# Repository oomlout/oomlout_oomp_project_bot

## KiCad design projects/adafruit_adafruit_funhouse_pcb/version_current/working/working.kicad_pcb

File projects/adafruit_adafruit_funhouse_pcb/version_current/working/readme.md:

# Adafruit-FunHouse-PCB by adafruit  
This is a harvested standardized copy of a project from github.  
The original project can be found at:  
https://github.com/adafruit/Adafruit-FunHouse-PCB  
Please consult that link for additional, details, files, and license information.  
Note: It was auto harvested and if the original repo had more than one board file or anything out of the ordinary the files here are likely not representative.

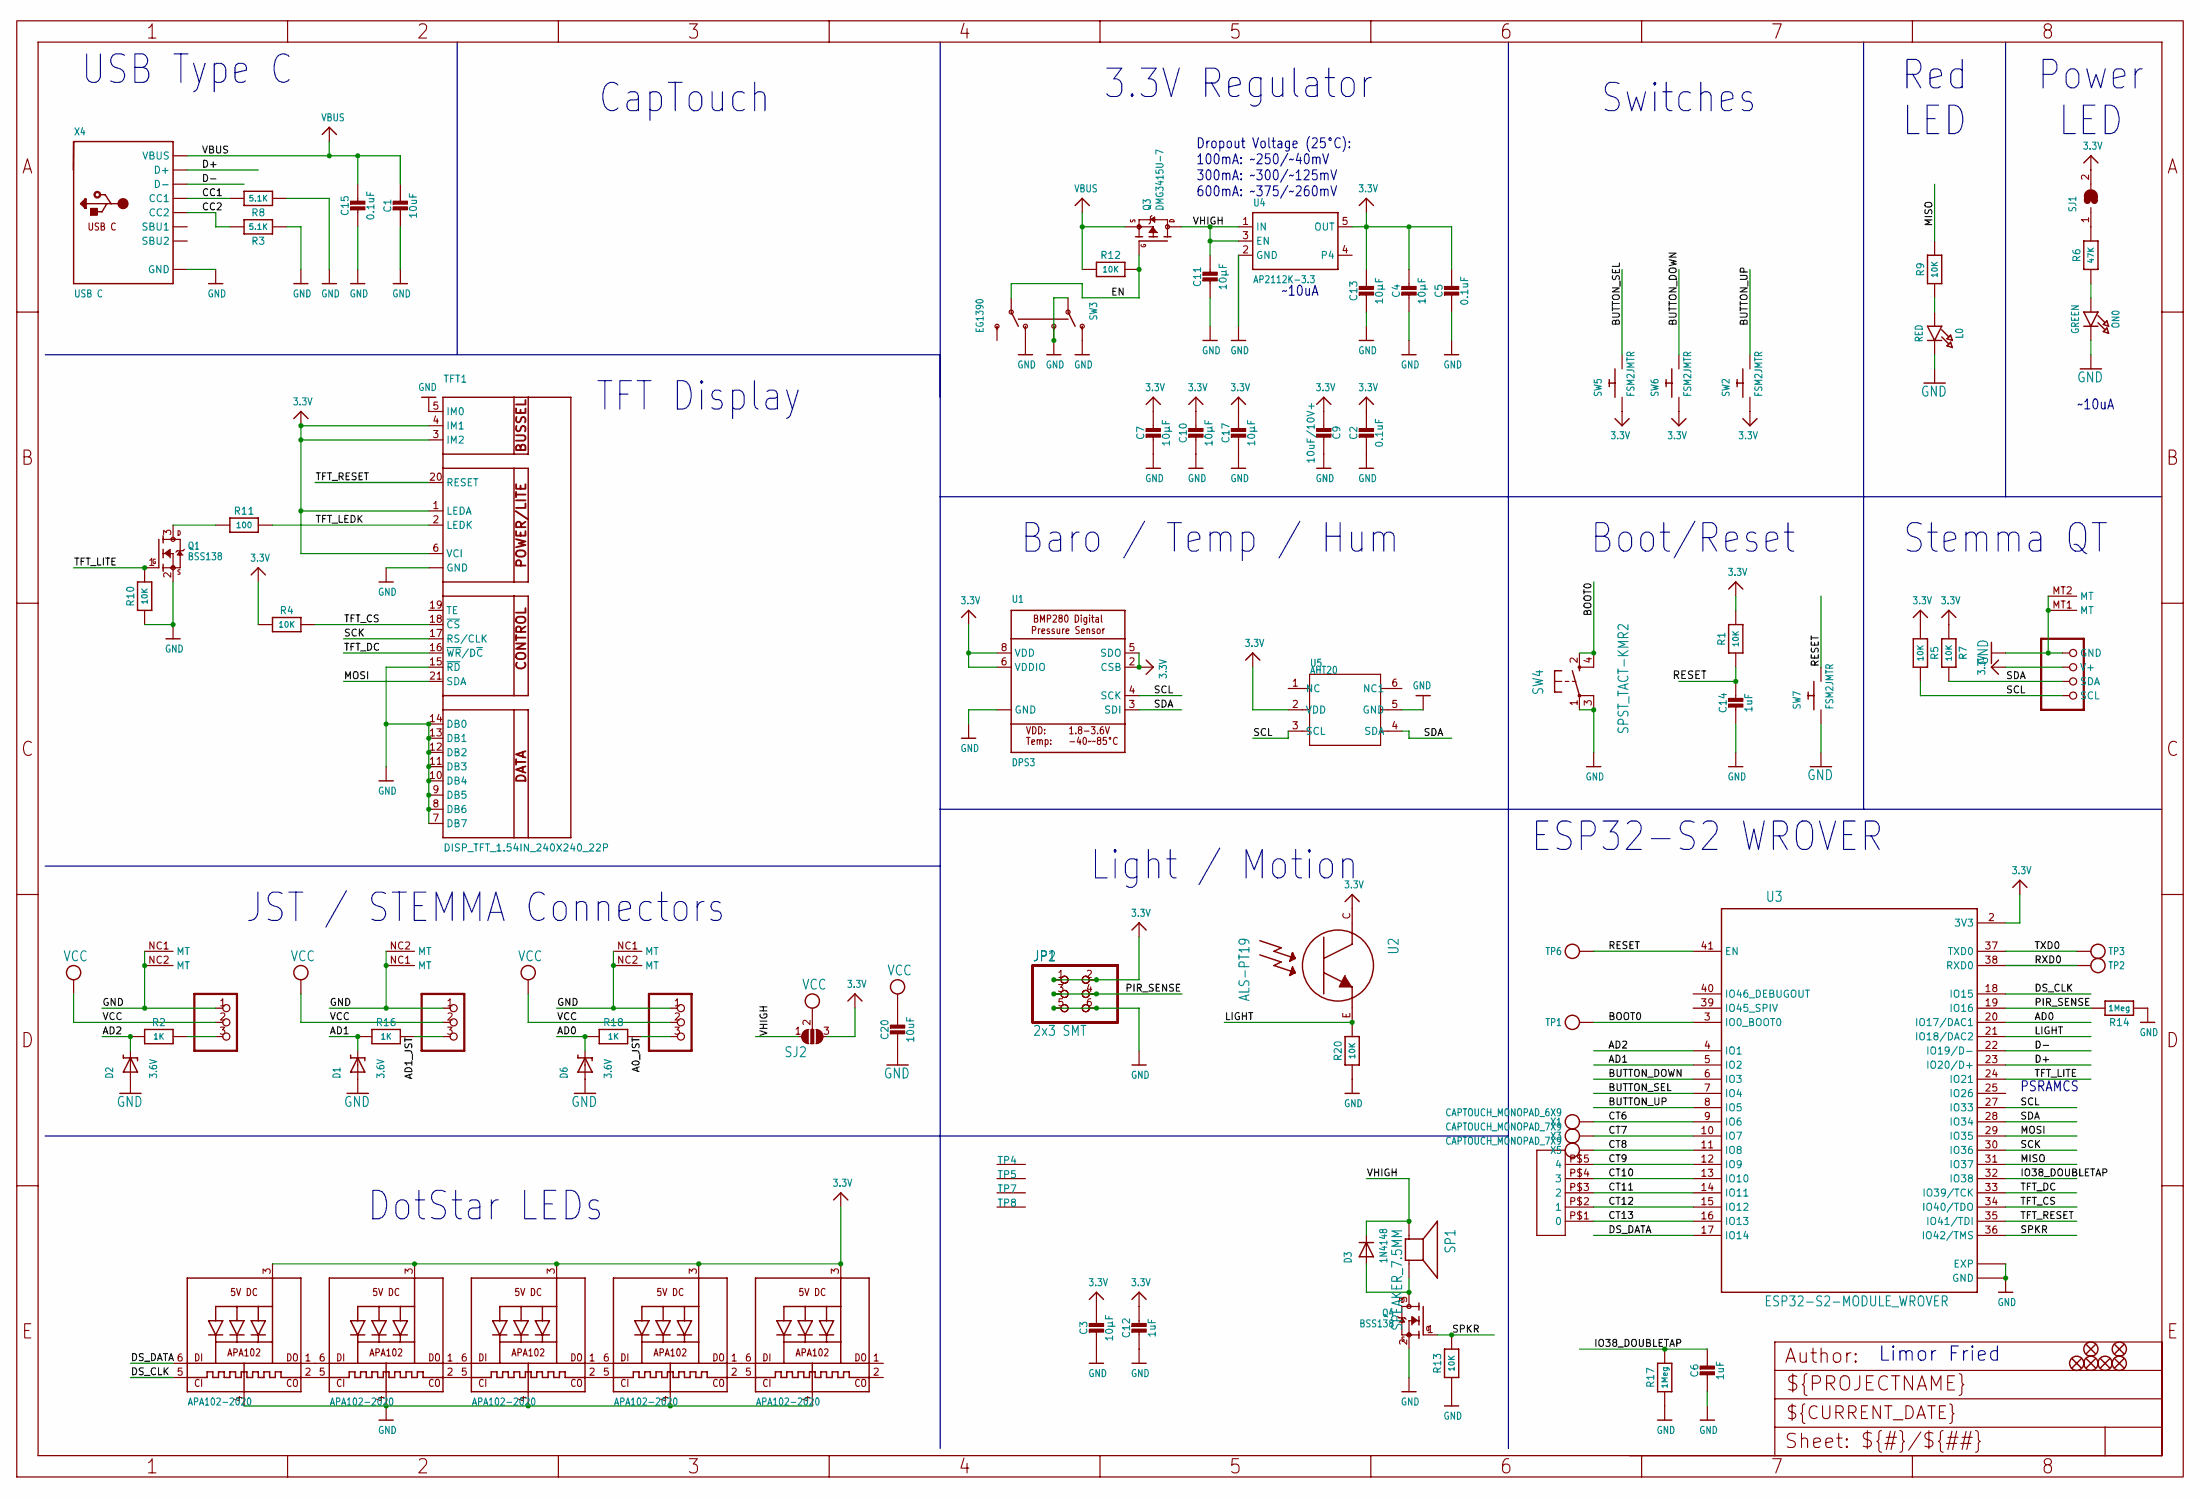
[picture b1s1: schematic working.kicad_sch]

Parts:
C1, C20: 10uF; 0805-NO
C2, C5, C15: 0.1uF; 0603-NO
C3, C4, C7, C10, C11, C13, C17: 10µF; 0805-NO
C6, C12, C14: 1uF; 0603-NO
C9: 10uF/10V+; 0805_10MGAP
CONN1: STEMMA_I2C_QT; JST_SH4
D1, D2, D6: 3.6V; SOD-323
D3: 1N4148; SOD-323F
DS0, DS1, DS2, DS3, DS4: APA102-2020; APA102_2020
FID1, FID2, FID3, FID4, FID5, FID6: FIDUCIAL_1MM
JP1: 2x3 SMT; 2X03_SMT_4UCON_14113
JP2: HEADER-2X3_SMTTHM; 2X03_SMTTHM
L0: RED; CHIPLED_0603_NOOUTLINE
ON0: GREEN; CHIPLED_0603_NOOUTLINE
Q1: BSS138; SOT23-WIDE
Q3: DMG3415U-7; SOT23-R
Q4: BSS138; SOT23-R
R1, R4, R5, R7, R9, R10, R12, R13, R20: 10K; 0603-NO
R2, R16, R18: 1K; 0603-NO
R3, R8: 5.1K; 0603-NO
R6: 47K; 0603-NO
R11: 100; 0603-NO
R14, R17: 1Meg; 0603-NO
SENSE0, SENSE1, SENSE3: JST PH 3; JSTPH3
SJ1: SOLDERJUMPERCLOSED; SOLDERJUMPER_CLOSEDWIRE
SJ2: SOLDERJUMPER_2WAY; SOLDERJUMPER_2WAY_OPEN_NOPASTE
SP1: SPEAKER_7.5MM; BUZZER_SMT_7.5MM
SW2, SW5, SW6, SW7: FSM2JMTR; TACTILE_3X6MM
SW3: EG1390
SW4: SPST_TACT-KMR2; KMR2
TFT1: DISP_TFT_1.54IN_240X240_22P; TFT_1.54IN_240X240_22PIN
TP1, TP2, TP3, TP6: TESTPOINTROUND1.5MMNO; TESTPOINT_ROUND_1.5MM_NO
TP4, TP5, TP7, TP8: SEWTAP_SMTNUTM3; SMT_NUT_3MM
U1: DPS3; BMX280_COMBO
U2: ALS-PT19; ALS-PT19-315C
U3: ESP32-S2-MODULE_WROVER; MODULE_ESP32-S2-WROVER
U4: AP2112K-3.3; SOT23-5
U5: AHT20; SNR6-1.0-3X3X1MM
X1: CAPTOUCH_MONOPAD_6X9; CAPTOUCH_6X9MM
X3, X5: CAPTOUCH_MONOPAD_7X9; CAPTOUCH_7X9MM
X4: USB C; USB_C_CUSB31-CFM2AX-01-X
X6: CAPTOUCH_5SLIDER_10MM; CAPTOUCH_5SLIDER

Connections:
3.3V: C2.1, C3.1, C4.1, C5.1, C7.1, C9.2, C10.1, C12.1, C13.1, C17.1, CONN1.2 (V+), DS0.3 (VDD), DS1.3 (VDD), DS2.3 (VDD), DS3.3 (VDD), DS4.3 (VDD), JP1.1, JP1.2, JP2.1, JP2.2, JP2.T1 (1), JP2.T2 (2), R1.2, R4.1, R5.1, R7.1, SJ1.2, SJ2.3, SW2.P$1, SW5.P$1, SW6.P$1, TFT1.1 (LEDA), TFT1.3 (IM2), TFT1.4 (IM1), TFT1.6 (VCI), U1.2 (CSB), U1.5 (SDO), U1.6 (VDDIO), U1.8 (VDD), U2.C, U3.2 (3V3), U4.5 (OUT), U5.2 (VDD)
A0_JST: R18.1, SENSE1.3
A2_JST2: R2.1, SENSE3.3
AD0: D6.C, R18.2, U3.20 (IO17/DAC1)
AD1: D1.C, R16.2, U3.5 (IO2)
AD1_JST: R16.1, SENSE0.3
AD2: D2.C, R2.2, U3.4 (IO1)
BOOT0: SW4.2 (S), SW4.4 (S1), TP1.P$1, U3.3 (IO0_BOOT0)
BUTTON_DOWN: SW6.P$2, U3.6 (IO3)
BUTTON_SEL: SW5.P$2, U3.7 (IO4)
BUTTON_UP: SW2.P$2, U3.8 (IO5)
CC1: R8.2, X4.A5 (CC1)
CC2: R3.2, X4.B5 (CC2)
CT6: U3.9 (IO6), X1.P$1
CT7: U3.10 (IO7), X3.P$1
CT8: U3.11 (IO8), X5.P$1
CT9: U3.12 (IO9), X6.P$5 (4)
CT10: U3.13 (IO10), X6.P$4 (3)
CT11: U3.14 (IO11), X6.P$3 (2)
CT12: U3.15 (IO12), X6.P$2 (1)
CT13: U3.16 (IO13), X6.P$1 (0)
D+: U3.23 (IO20/D+), X4.A6 (D+), X4.B6 (D+)
D-: U3.22 (IO19/D-), X4.A7 (D-), X4.B7 (D-)
DS_CLK: DS0.5 (CKI), U3.18 (IO15)
DS_DATA: DS0.6 (DI), U3.17 (IO14)
EN: Q3.1 (G), R12.2, SW3.P2
GND: C1.2, C2.2, C3.2, C4.2, C5.2, C6.2, C7.2, C9.1, C10.2, C11.2, C12.2, C13.2, C14.2, C15.2, C17.2, C20.2, CONN1.1 (GND), CONN1.MT1 (MT), CONN1.MT2 (MT), D1.A, D2.A, D6.A, DS0.4 (GND), DS1.4 (GND), DS2.4 (GND), DS3.4 (GND), DS4.4 (GND), JP1.5, JP1.6, JP2.5, JP2.6, JP2.T5 (5), JP2.T6 (6), L0.C, ON0.C, Q1.2 (S), Q4.2 (S), R3.1, R8.1, R10.1, R13.1, R14.1, R17.1, R20.1, SENSE0.1, SENSE0.NC1 (MT), SENSE0.NC2 (MT), SENSE1.1, SENSE1.NC1 (MT), SENSE1.NC2 (MT), SENSE3.1, SENSE3.NC1 (MT), SENSE3.NC2 (MT), SW3.O1, SW3.O2, SW3.P1, SW3.S1, SW4.1, SW4.3 (P1), SW7.P$1, TFT1.5 (IM0), TFT1.7 (DB7), TFT1.8 (DB6), TFT1.9 (DB5), TFT1.10 (DB4), TFT1.11 (DB3), TFT1.12 (DB2), TFT1.13 (DB1), TFT1.14 (DB0), TFT1.15 (~RD), TFT1.22 (GND), TFT1.SUPPORT1 (GND), TFT1.SUPPORT2 (GND), U1.1 (GND), U1.7 (GND), U3.1 (GND), U3.26 (GND), U3.42 (GND), U3.43_1 (EXP), U3.43_2 (EXP), U3.43_3 (EXP), U3.43_4 (EXP), U3.43_5 (EXP), U3.43_6 (EXP), U3.43_7 (EXP), U3.43_8 (EXP), U3.43_9 (EXP), U3.43_10 (EXP), U3.43_11 (EXP), U3.43_12 (EXP), U3.43_13 (EXP), U3.43_14 (EXP), U3.43_15 (EXP), U3.43_16 (EXP), U3.43_17 (EXP), U3.43_18 (EXP), U3.43_19 (EXP), U3.43_20 (EXP), U3.43_21 (EXP), U4.2 (GND), U5.5 (GND), X4.A1B12 (GND), X4.B1A12 (GND)
IO38_DOUBLETAP: C6.1, R17.2, U3.32 (IO38)
LIGHT: R20.2, U2.E, U3.21 (IO18/DAC2)
MISO: R9.2, U3.31 (IO37)
MOSI: TFT1.21 (SDA), U3.29 (IO35)
unnamed: L0.A, R9.1
unnamed: R6.2, SJ1.1
unnamed: ON0.A, R6.1
unnamed: D3.A, Q4.3 (D), SP1.-
unnamed: DS0.1 (DO), DS1.6 (DI)
unnamed: DS0.2 (CKO), DS1.5 (CKI)
unnamed: DS1.1 (DO), DS2.6 (DI)
unnamed: DS1.2 (CKO), DS2.5 (CKI)
unnamed: DS2.1 (DO), DS3.6 (DI)
unnamed: DS2.2 (CKO), DS3.5 (CKI)
unnamed: DS3.1 (DO), DS4.6 (DI)
unnamed: DS3.2 (CKO), DS4.5 (CKI)
unnamed: Q1.3 (D), R11.1
PIR_SENSE: JP1.3, JP1.4, JP2.3, JP2.4, JP2.T3 (3), JP2.T4 (4), R14.2, U3.19 (IO16)
RESET: C14.1, R1.1, SW7.P$2, TP6.P$1, U3.41 (EN)
RXD0: TP2.P$1, U3.38 (RXD0)
SCK: TFT1.17 (RS/CLK), U3.30 (IO36)
SCL: CONN1.4 (SCL), R5.2, U1.4 (SCK), U3.27 (IO33), U5.3 (SCL)
SDA: CONN1.3 (SDA), R7.2, U1.3 (SDI), U3.28 (IO34), U5.4 (SDA)
SPKR: Q4.1 (G), R13.2, U3.36 (IO42/TMS)
TFT_CS: R4.2, TFT1.18 (~CS), U3.34 (IO40/TDO)
TFT_DC: TFT1.16 (~WR/D~C), U3.33 (IO39/TCK)
TFT_LEDK: R11.2, TFT1.2 (LEDK)
TFT_LITE: Q1.1 (G), R10.2, U3.24 (IO21)
TFT_RESET: TFT1.20 (RESET), U3.35 (IO41/TDI)
TXD0: TP3.P$1, U3.37 (TXD0)
VBUS: C1.1, C15.1, Q3.2 (S), R12.1, X4.A4B9 (VBUS), X4.B4A9 (VBUS)
VCC: C20.1, SENSE0.2, SENSE1.2, SENSE3.2, SJ2.2
VHIGH: C11.1, D3.C, Q3.3 (D), SJ2.1, SP1.+, U4.1 (IN), U4.3 (EN)

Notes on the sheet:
Baro / Temp / Hum
~10uA
JST / STEMMA Connectors
CapTouch
ESP32-S2 WROVER
Red LED
3.3V Regulator
Dropout Voltage (25°C): 100mA: ~250/~40mV 300mA: ~300/~125mV 600mA: ~375/~260mV
Stemma QT
PSRAMCS
Limor Fried
Boot/Reset
Switches
DotStar LEDs
USB Type C
TFT Display
Power LED
Light / Motion

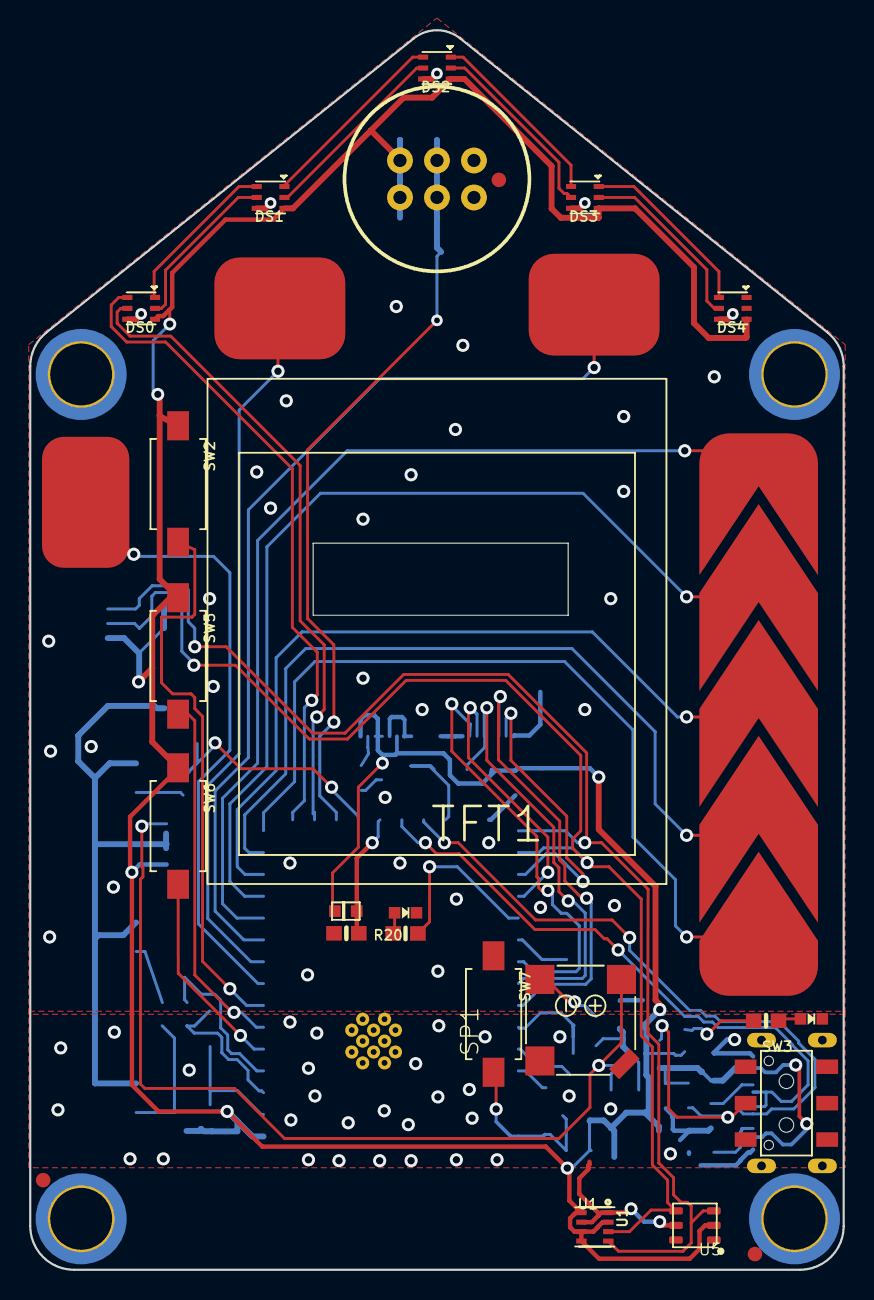
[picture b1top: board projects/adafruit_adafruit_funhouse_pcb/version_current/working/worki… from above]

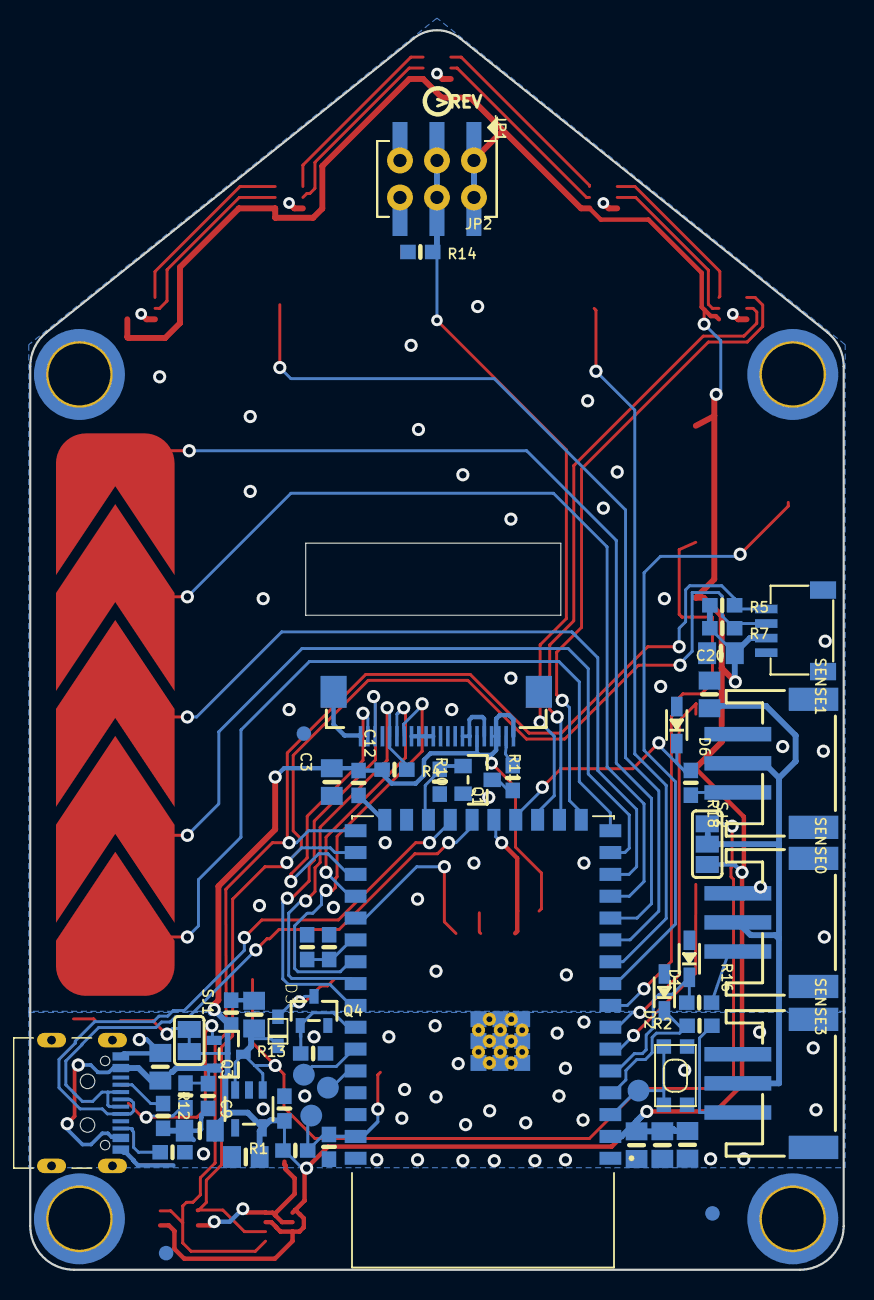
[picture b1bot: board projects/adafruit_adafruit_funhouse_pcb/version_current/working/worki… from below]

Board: 2 copper layers, 55.9 x 85.1 mm, 91 parts (63 on the bottom side), 60 nets.

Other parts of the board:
U$41: PCBFEAT-REV-040
U$45: FUNHOUSE_FRONT
U$69: FUNHOUSE_BACK

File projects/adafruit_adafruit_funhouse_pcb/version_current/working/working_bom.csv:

Row,Description,Part,References,Value,Footprint,Quantity Per PCB,Status,Datasheet
1,,CAP_CERAMIC0603_NO,C2 C5 C15,0.1uF,0603-NO,3, ,
2,,CAP_CERAMIC0603_NO,C6 C12 C14,1uF,0603-NO,3, ,
3,,CAP_CERAMIC0805-NOOUTLINE,C1 C3 C4 C7 C10 C11 C13 C17 C20,10uF,0805-NO,9, ,
4,,CAP_CERAMIC0805_10MGAP,C9,10uF/10V+,0805_10MGAP,1, ,
5,,STEMMA_I2C_QT,CONN1,STEMMA_I2C_QT,JST_SH4,1, ,
6,,DIODESOD-323F,D3,1N4148,SOD-323F,1, ,
7,,DIODE-ZENERSOD323,D1 D2 D6,3.6V,SOD-323,3, ,
8,,APA1022020,DS0 DS1 DS2 DS3 DS4,APA102-2020,APA102_2020,5, ,
9,,HEADER-2X314113,JP1,2x3 SMT,2X03_SMT_4UCON_14113,1, ,
10,,HEADER-2X3_SMTTHM,JP2,HEADER-2X3_SMTTHM,2X03_SMTTHM,1, ,
11,,LED0603_NOOUTLINE,L0,RED,CHIPLED_0603_NOOUTLINE,1, ,
12,,LED0603_NOOUTLINE,ON0,GREEN,CHIPLED_0603_NOOUTLINE,1, ,
13,,MOSFET-NWIDE,Q1,BSS138,SOT23-WIDE,1, ,
14,,MOSFET-NREFLOW,Q4,BSS138,SOT23-R,1, ,
15,,MOSFET-P,Q3,DMG3415U-7,SOT23-R,1, ,
16,,RESISTOR_0603_NOOUT,R11,100,0603-NO,1, ,
17,,RESISTOR_0603_NOOUT,R2 R16 R18,1K,0603-NO,3, ,
18,,RESISTOR_0603_NOOUT,R3 R8,5.1K,0603-NO,2, ,
19,,RESISTOR_0603_NOOUT,R1 R4 R5 R7 R9 R10 R12 R13 R20,10K,0603-NO,9, ,
20,,RESISTOR_0603_NOOUT,R6,47K,0603-NO,1, ,
21,,RESISTOR_0603_NOOUT,R14 R17,1Meg,0603-NO,2, ,
22,,CON_JST_PH_3PIN,SENSE0 SENSE1 SENSE3,JST PH 3,JSTPH3,3, ,
23,,SPEAKER_7.5MM,SP1,SPEAKER_7.5MM,BUZZER_SMT_7.5MM,1, ,
24,,SWITCH_DPDTEG1390,SW3,EG1390,EG1390,1, ,
25,,adafruit_electromech_SWITCH_PUSHBUTTON_3.5X6MM,SW2 SW5 SW6,FSM2JMTR,TACTILE_3X6MM,3, ,
26,,SWITCH_PUSHBUTTON_3.5X6MM,SW7,FSM2JMTR,TACTILE_3X6MM,1, ,
27,,SPST_TACT-KMR2,SW4,SPST_TACT-KMR2,KMR2,1, ,
28,,DISP_TFT_1.54IN_240X240_22P,TFT1,DISP_TFT_1.54IN_240X240_22P,TFT_1.54IN_240X240_22PIN,1, ,
29,,SENSOR-AHT20,U5,AHT20,SNR6-1.0-3X3X1MM,1, ,
30,,PHOTOTRANSISTOR_PT19-315C,U2,ALS-PT19,ALS-PT19-315C,1, ,
31,,VREG_SOT23-5,U4,AP2112K-3.3,SOT23-5,1, ,
32,,BMP280_COMBO,U1,DPS3,BMX280_COMBO,1, ,
33,,ESP32-S2-MODULE_WROVER,U3,ESP32-S2-MODULE_WROVER,MODULE_ESP32-S2-WROVER,1, ,
34,,CAPTOUCH_5SLIDER_10MM,X6,CAPTOUCH_5SLIDER_10MM,CAPTOUCH_5SLIDER,1, ,
35,,CAPTOUCH_MONOPAD_6X9,X1,CAPTOUCH_MONOPAD_6X9,CAPTOUCH_6X9MM,1, ,
36,,CAPTOUCH_MONOPAD_7X9,X3 X5,CAPTOUCH_MONOPAD_7X9,CAPTOUCH_7X9MM,2, ,
37,,USB_C,X4,USB C,USB_C_CUSB31-CFM2AX-01-X,1, ,





Project info:
Schematic:,working
Variant:,default
Revision:,
Date:,2023-08-06_12-55-57
KiCad Version:,7.0.6-7.0.6~ubuntu22.04.1
Statistics:
Component Groups:,37
Component Count:,72 (0 SMD/ 0 THT)
Fitted Components:,72 (0 SMD/ 0 THT)
Number of PCBs:,1
Total Components:,72

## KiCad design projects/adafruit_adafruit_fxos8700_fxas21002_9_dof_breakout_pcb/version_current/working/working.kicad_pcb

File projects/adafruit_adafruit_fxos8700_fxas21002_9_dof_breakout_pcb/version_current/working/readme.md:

# Adafruit-FXOS8700-FXAS21002-9-DoF-Breakout-PCB by adafruit  
This is a harvested standardized copy of a project from github.  
The original project can be found at:  
https://github.com/adafruit/Adafruit-FXOS8700-FXAS21002-9-DoF-Breakout-PCB  
Please consult that link for additional, details, files, and license information.  
Note: It was auto harvested and if the original repo had more than one board file or anything out of the ordinary the files here are likely not representative.

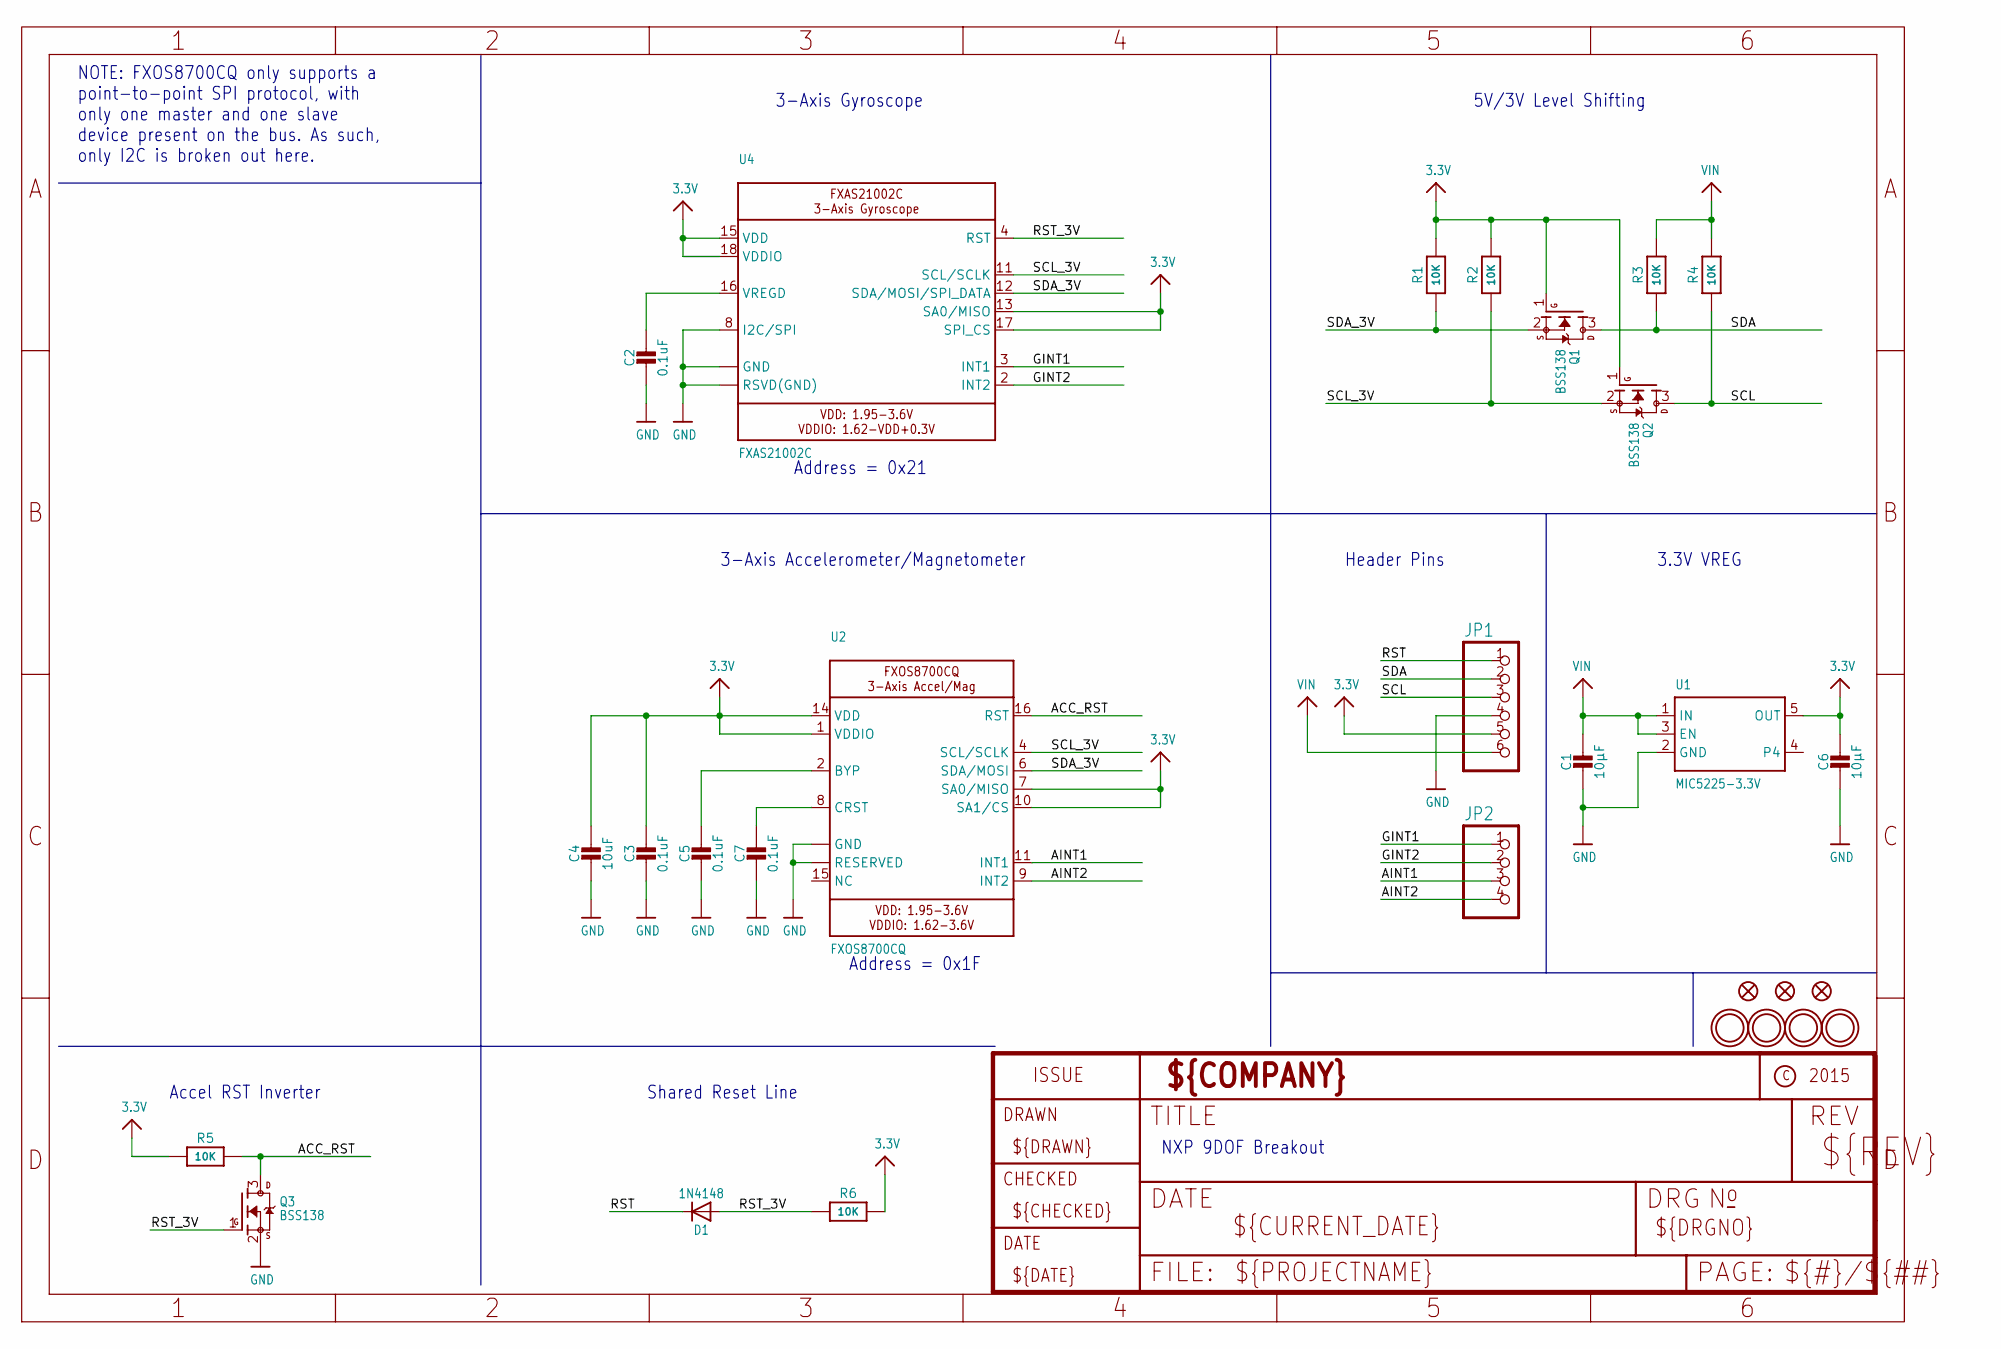
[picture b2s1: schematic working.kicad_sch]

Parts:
C1, C6: 10µF; 0805-NO
C2, C3, C5, C7: 0.1uF; 0805-NO
C4: 10uF; 0805-NO
D1: 1N4148; SOD-323
FID1, FID2, FID3: FIDUCIAL_1MM
JP1: HEADER-1X670MIL; 1X06_ROUND_70
JP2: HEADER-1X4ROUND; 1X04_ROUND
Q1, Q2, Q3: BSS138; SOT23-WIDE
R1, R2, R3, R4, R5, R6: 10K; 0805-NO
U1: MIC5225-3.3V; SOT23-5
U2: FXOS8700CQ; QFN16_3MM_FREESCALE_5X3
U4: FXAS21002C; QFN24_4MM_FREESCALE_7X5
U$1, U$2, U$3, U$4: MOUNTINGHOLE2.5; MOUNTINGHOLE_2.5_PLATED

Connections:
3.3V: C3.1, C4.1, C6.1, JP1.5, Q1.1 (G), Q2.1 (G), R1.2, R2.2, R5.1, R6.2, U1.5 (OUT), U2.1 (VDDIO), U2.7 (SA0/MISO), U2.10 (SA1/CS), U2.14 (VDD), U4.13 (SA0/MISO), U4.15 (VDD), U4.17 (SPI_CS), U4.18 (VDDIO)
ACC_RST: Q3.3 (D), R5.2, U2.16 (RST)
AINT1: JP2.3, U2.11 (INT1)
AINT2: JP2.4, U2.9 (INT2)
GINT1: JP2.1, U4.3 (INT1)
GINT2: JP2.2, U4.2 (INT2)
GND: C1.2, C2.2, C3.2, C4.2, C5.2, C6.2, C7.2, JP1.4, Q3.2 (S), U1.2 (GND), U2.3 (RESERVED), U2.5 (GND), U2.12 (GND), U2.13 (RESERVED), U4.1 (GND), U4.5 (GND), U4.6 (RSVD(GND)), U4.7 (RSVD(GND)), U4.8 (I2C/SPI), U4.9 (RSVD(GND)), U4.10 (RSVD(GND)), U4.14 (GND), U4.19 (GND), U4.20 (RSVD(GND)), U4.21 (RSVD(GND)), U4.22 (RSVD(GND)), U4.23 (RSVD(GND)), U4.24 (RSVD(GND))
unnamed: C2.1, U4.16 (VREGD)
unnamed: C5.1, U2.2 (BYP)
unnamed: C7.1, U2.8 (CRST)
RST: D1.C, JP1.1
RST_3V: D1.A, Q3.1 (G), R6.1, U4.4 (RST)
SCL: JP1.3, Q2.3 (D), R4.1
SCL_3V: Q2.2 (S), R2.1, U2.4 (SCL/SCLK), U4.11 (SCL/SCLK)
SDA: JP1.2, Q1.3 (D), R3.1
SDA_3V: Q1.2 (S), R1.1, U2.6 (SDA/MOSI), U4.12 (SDA/MOSI/SPI_DATA)
VIN: C1.1, JP1.6, R3.2, R4.2, U1.1 (IN), U1.3 (EN)

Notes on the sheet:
Address = 0x21
Address = 0x1F
3-Axis Accelerometer/Magnetometer
5V/3V Level Shifting
3-Axis Gyroscope
Shared Reset Line
3.3V VREG
NXP 9DOF Breakout
Accel RST Inverter
NOTE: FXOS8700CQ only supports a point-to-point SPI protocol, with only one master and one slave device present on the bus. As such, only I2C is broken out here.
Header Pins

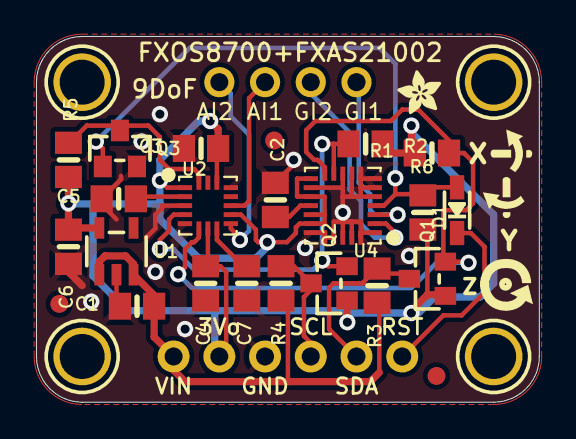
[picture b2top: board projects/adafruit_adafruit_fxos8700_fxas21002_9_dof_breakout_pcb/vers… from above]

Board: 2 copper layers, 27.9 x 20.3 mm, 34 parts (1 on the bottom side), 17 nets.

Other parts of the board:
U$26: ADAFRUIT_2.5MM
U$27: SYMBOL_GYRO_CCLOCKWISE
U$28: SYMBOL_GYRO_CLOCKWISE
U$31: SYMBOL_GYRO_Z
U$32: PCBFEAT-REV-040

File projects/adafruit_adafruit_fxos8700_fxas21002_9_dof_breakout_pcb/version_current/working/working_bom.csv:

Row,Description,Part,References,Value,Footprint,Quantity Per PCB,Status,Datasheet
1,,CAP_CERAMIC0805-NOOUTLINE,C2 C3 C5 C7,0.1uF,0805-NO,4, ,
2,,CAP_CERAMIC0805-NOOUTLINE,C1 C4 C6,10µF,0805-NO,3, ,
3,,DIODESOD-323,D1,1N4148,SOD-323,1, ,
4,,HEADER-1X4ROUND,JP2,HEADER-1X4ROUND,1X04_ROUND,1, ,
5,,HEADER-1X670MIL,JP1,HEADER-1X670MIL,1X06_ROUND_70,1, ,
6,,MOSFET-NWIDE,Q1 Q2 Q3,BSS138,SOT23-WIDE,3, ,
7,,RESISTOR0805_NOOUTLINE,R1 R2 R3 R4 R5 R6,10K,0805-NO,6, ,
8,,GYRO_FXAS21002C,U4,FXAS21002C,QFN24_4MM_FREESCALE_7X5,1, ,
9,,ACCEL_MAG_FXOS8700CQ,U2,FXOS8700CQ,QFN16_3MM_FREESCALE_5X3,1, ,
10,,VREG_SOT23-5,U1,MIC5225-3.3V,SOT23-5,1, ,





Project info:
Schematic:,working
Variant:,default
Revision:,
Date:,2023-08-03_17-21-22
KiCad Version:,7.0.6-7.0.6~ubuntu22.04.1
Statistics:
Component Groups:,10
Component Count:,22 (0 SMD/ 0 THT)
Fitted Components:,22 (0 SMD/ 0 THT)
Number of PCBs:,1
Total Components:,22

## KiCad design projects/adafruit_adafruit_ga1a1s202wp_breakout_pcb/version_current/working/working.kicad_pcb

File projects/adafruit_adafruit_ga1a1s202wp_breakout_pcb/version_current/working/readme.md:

# Adafruit-GA1A1S202WP-Breakout-PCB by adafruit  
This is a harvested standardized copy of a project from github.  
The original project can be found at:  
https://github.com/adafruit/Adafruit-GA1A1S202WP-Breakout-PCB  
Please consult that link for additional, details, files, and license information.  
Note: It was auto harvested and if the original repo had more than one board file or anything out of the ordinary the files here are likely not representative.

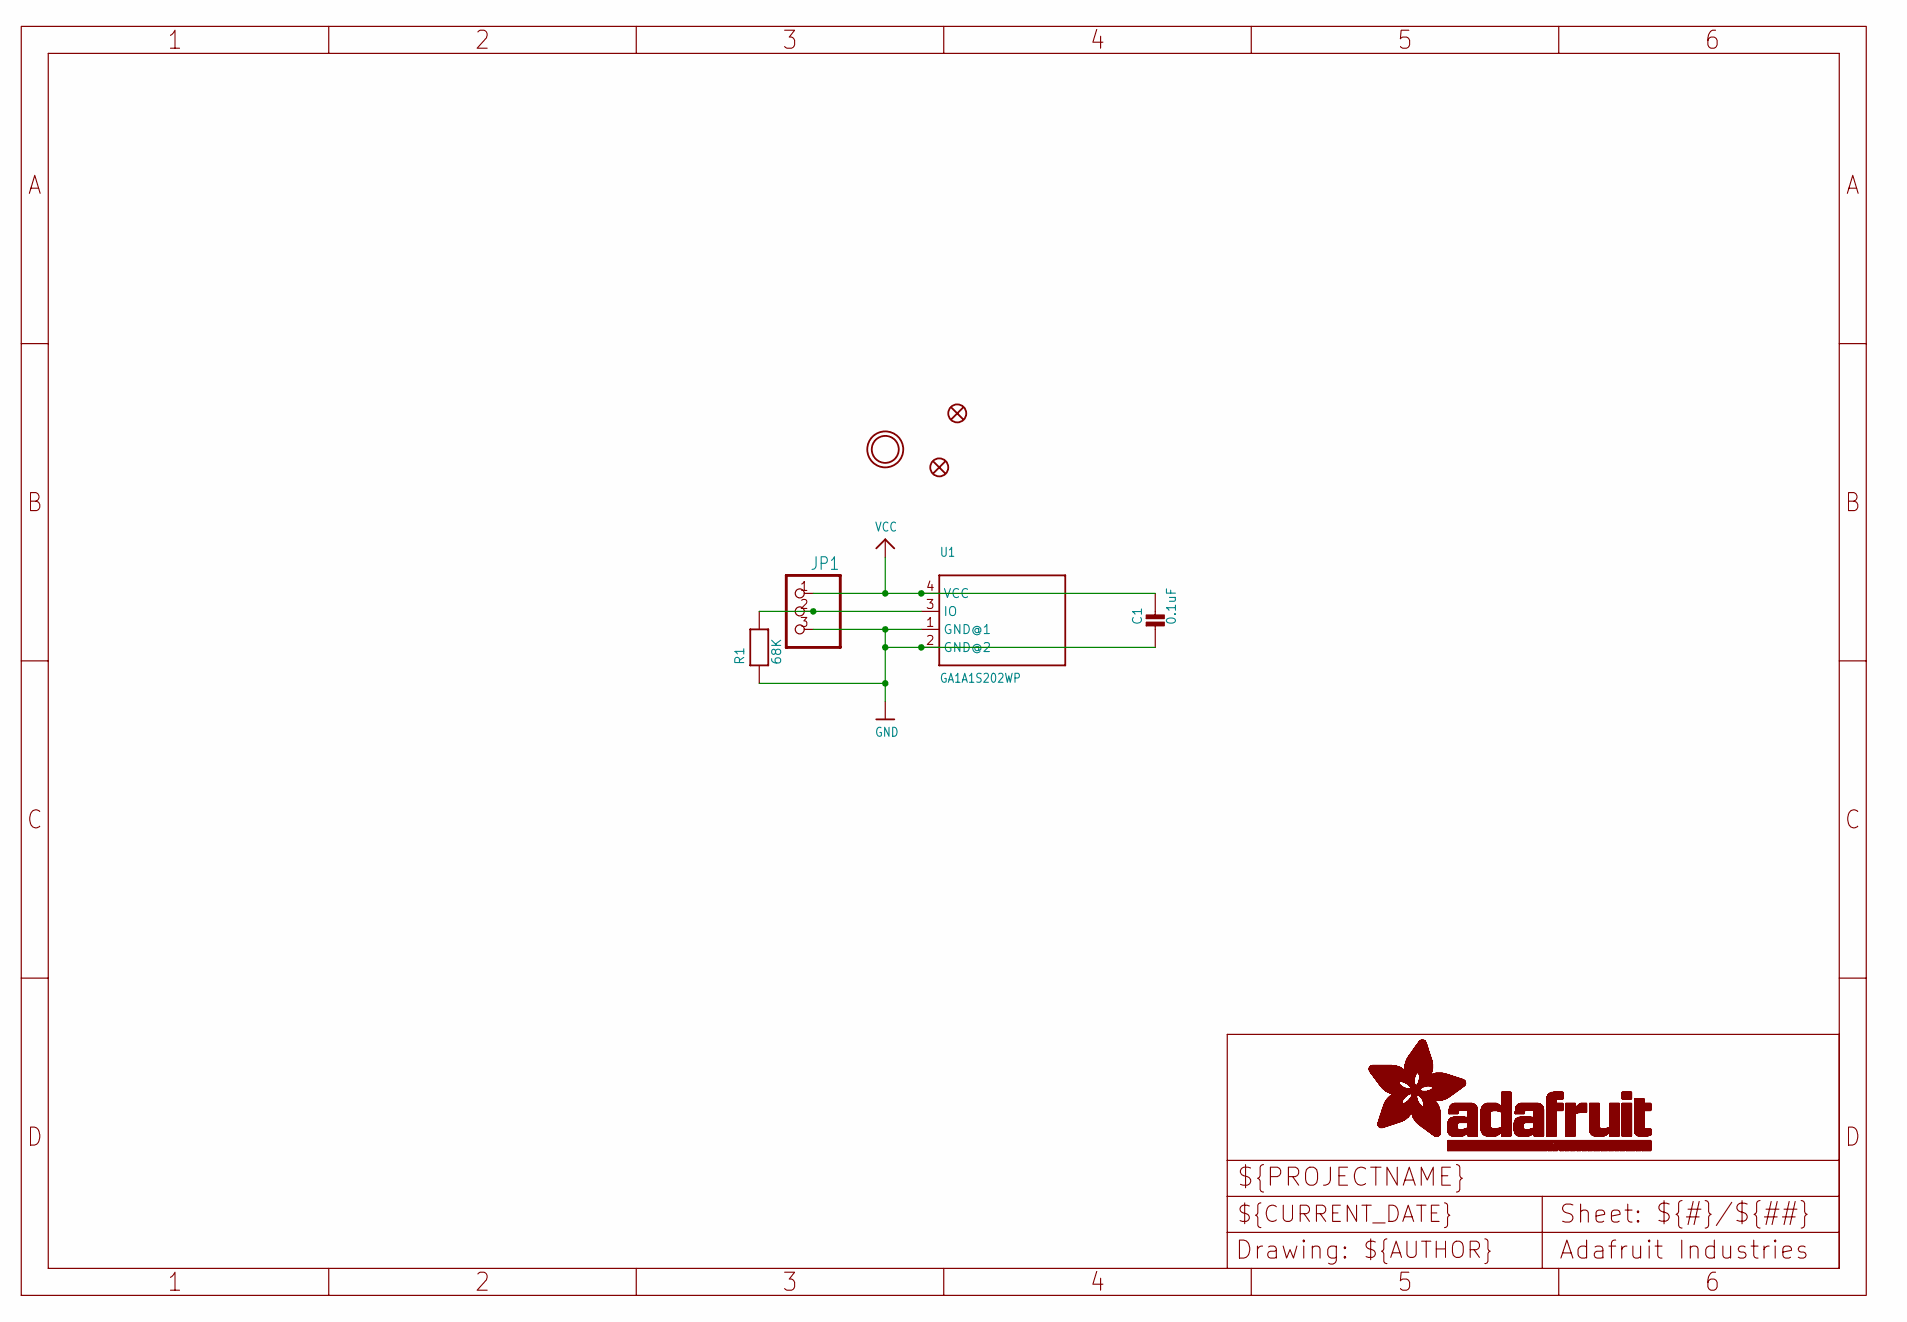
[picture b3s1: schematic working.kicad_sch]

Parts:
C1: 0.1uF; _0805MP
FID1, FID2: FIDUCIAL""; FIDUCIAL_1MM
JP1: HEADER-1X3ROUND; 1X03_ROUND
R1: 68K; _0805MP
U1: GA1A1S202WP
U$3: MOUNTINGHOLE2.5; MOUNTINGHOLE_2.5_PLATED

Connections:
GND: C1.2, JP1.3, R1.1, U1.1 (GND@1), U1.2 (GND@2)
unnamed: JP1.2, R1.2, U1.3 (IO)
VCC: C1.1, JP1.1, U1.4 (VCC)

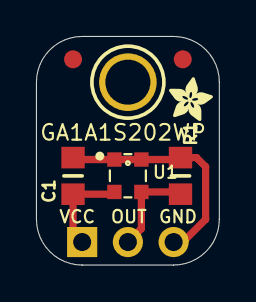
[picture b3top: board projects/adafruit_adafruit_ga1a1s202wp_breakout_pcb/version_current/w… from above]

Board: 2 copper layers, 10.2 x 12.7 mm, 8 parts (0 on the bottom side), 3 nets.

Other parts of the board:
U$4: ADAFRUIT_2.5MM

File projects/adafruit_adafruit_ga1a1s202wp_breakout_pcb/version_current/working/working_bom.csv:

Row,Description,Part,References,Value,Footprint,Quantity Per PCB,Status,Datasheet
1,,CAP_CERAMIC_0805MP,C1,0.1uF,_0805MP,1, ,
2,,HEADER-1X3ROUND,JP1,HEADER-1X3ROUND,1X03_ROUND,1, ,
3,,RESISTOR_0805MP,R1,68K,_0805MP,1, ,
4,,GA1A1S202WP,U1,GA1A1S202WP,GA1A1S202WP,1, ,





Project info:
Schematic:,working
Variant:,default
Revision:,
Date:,2023-08-03_17-21-22
KiCad Version:,7.0.6-7.0.6~ubuntu22.04.1
Statistics:
Component Groups:,4
Component Count:,4 (0 SMD/ 0 THT)
Fitted Components:,4 (0 SMD/ 0 THT)
Number of PCBs:,1
Total Components:,4

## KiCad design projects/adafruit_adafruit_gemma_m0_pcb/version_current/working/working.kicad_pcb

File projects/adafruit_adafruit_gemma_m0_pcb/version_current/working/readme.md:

# Adafruit-Gemma-M0-PCB by adafruit  
This is a harvested standardized copy of a project from github.  
The original project can be found at:  
https://github.com/adafruit/Adafruit-Gemma-M0-PCB  
Please consult that link for additional, details, files, and license information.  
Note: It was auto harvested and if the original repo had more than one board file or anything out of the ordinary the files here are likely not representative.

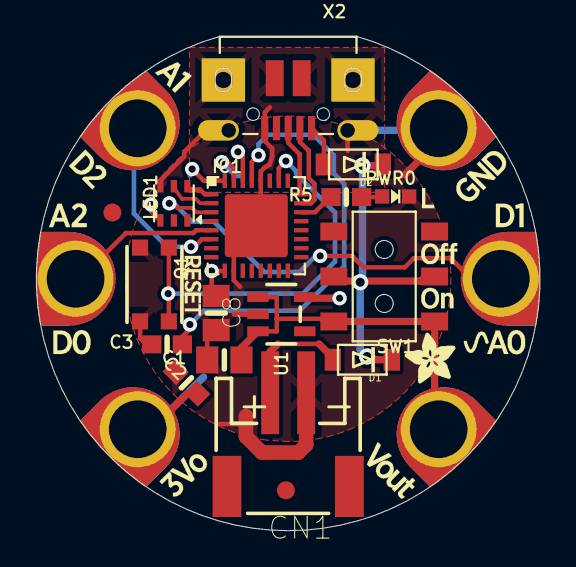
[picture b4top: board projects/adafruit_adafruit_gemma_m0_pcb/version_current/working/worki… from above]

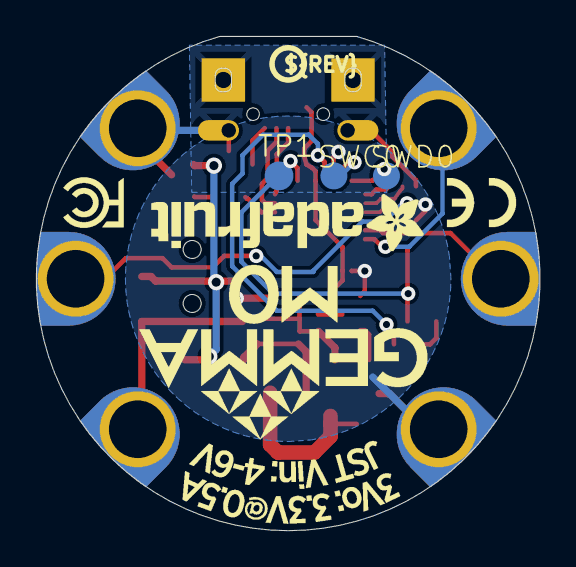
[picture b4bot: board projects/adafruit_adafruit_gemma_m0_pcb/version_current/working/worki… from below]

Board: 16 copper layers, 28.0 x 27.5 mm, 29 parts (5 on the bottom side), 19 nets.

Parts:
B0, B1, B2: SEWTAP-ALLIGATOR; SEWALLI
C1, C8: 10uF; 0805-NO
C2, C3: 1uF; 0603-NO
CN1: JST-PH; JSTPH2
D1, D2: SCHOTTKY; SOD-123FL
GND0: SEWTAP-ALLIGATOR; SEWALLI
IC1: ATSAMD21E; QFN32_5MM
LED1: AP102-2020; APA102_2020
PWR0: red; CHIPLED_0603_NOOUTLINE
Q1: reset; BTN_KMR2_4.6X2.8
R5: 1K; 0603-NO
SW1: EG1218; EG1390
SWC0: TPTP15R; TP15R
SWD0: TPTP15R; TP15R
TP1: TPTP16R; TP16R
U1: AP2112K-3.3; SOT23-5
U$1, U$6: FIDUCIAL_1MM
U$7: GEMMA_M0_BOTTOM
U$8: GEMMA_M0_TOP
U$10: PCBFEAT-REV-040
UNK3V3: SEWTAP-ALLIGATOR; SEWALLI
VBAT0: SEWTAP-ALLIGATOR; SEWALLI
X2: MicroUSB; 4UCONN_20329_V2

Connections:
3.3V: C2.1, C8.1, IC1.9, IC1.30, LED1.3, U1.5, UNK3V3.P$1
D0_SDA_TX: B0.P$1, IC1.5
D1_A0: B1.P$1, IC1.3
D2_SCL_RX: B2.P$1, IC1.6
D3: IC1.1, LED1.6
D4: IC1.2, LED1.5
D13: IC1.22, R5.2
D+: IC1.24, X2.D+
D-: IC1.23, X2.D-
GND: C1.2, C2.2, C3.2, C8.2, CN1.1, GND0.P$1, IC1.10, IC1.28, IC1.33, LED1.4, PWR0.C, Q1.B, Q1.B', U1.2, X2.BASE@1, X2.BASE@2, X2.GND, X2.SPRT@1, X2.SPRT@2, X2.SPRT@3, X2.SPRT@4
unnamed: PWR0.A, R5.1
SWCLK: IC1.31, SWC0.TP
SWDIO: IC1.32, SWD0.TP
VBAT: CN1.2, D1.A
VBUS: D2.A, X2.VBUS
VDDCORE: C3.1, IC1.29
VHIGH: D1.C, D2.C, SW1.P1, SW1.P2
VOUT: C1.1, SW1.O1, SW1.O2, U1.1, U1.3, VBAT0.P$1
~RESET: IC1.26, Q1.A, Q1.A', TP1.TP

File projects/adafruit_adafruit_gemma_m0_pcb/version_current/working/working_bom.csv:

Row,Description,Part,References,Value,Footprint,Quantity Per PCB,Status,Datasheet
1,,SEWTAP-ALLIGATOR,B0 B1 B2 GND0 UNK3V3 VBAT0,SEWTAP-ALLIGATOR,SEWALLI,6, ,
2,,CAP_CERAMIC0603_NO,C2 C3,1uF,0603-NO,2, ,
3,,CAP_CERAMIC0805-NOOUTLINE,C1 C8,10uF,0805-NO,2, ,
4,,CON_JST_PH_2PIN,CN1,JST-PH,JSTPH2,1, ,
5,,DIODE_SOD-123FL,D1 D2,SCHOTTKY,SOD-123FL,2, ,
6,,ATSAMD21E,IC1,ATSAMD21E,QFN32_5MM,1, ,
7,,APA1022020,LED1,AP102-2020,APA102_2020,1, ,
8,,LED0603_NOOUTLINE,PWR0,red,CHIPLED_0603_NOOUTLINE,1, ,
9,,SWITCH_TACT_SMT4.6X2.8,Q1,reset,BTN_KMR2_4.6X2.8,1, ,
10,,RESISTOR_0603_NOOUT,R5,1K,0603-NO,1, ,
11,,SWITCH_DPDTEG1390,SW1,EG1218,EG1390,1, ,
12,,TPTP15R,SWC0 SWD0,TPTP15R,TP15R,2, ,
13,,VREG_SOT23-5,U1,AP2112K-3.3,SOT23-5,1, ,
14,,USB_MICRO_20329_V2,X2,MicroUSB,4UCONN_20329_V2,1, ,





Project info:
Schematic:,working
Variant:,default
Revision:,
Date:,2023-08-03_17-21-22
KiCad Version:,7.0.6-7.0.6~ubuntu22.04.1
Statistics:
Component Groups:,14
Component Count:,23 (0 SMD/ 0 THT)
Fitted Components:,23 (0 SMD/ 0 THT)
Number of PCBs:,1
Total Components:,23
